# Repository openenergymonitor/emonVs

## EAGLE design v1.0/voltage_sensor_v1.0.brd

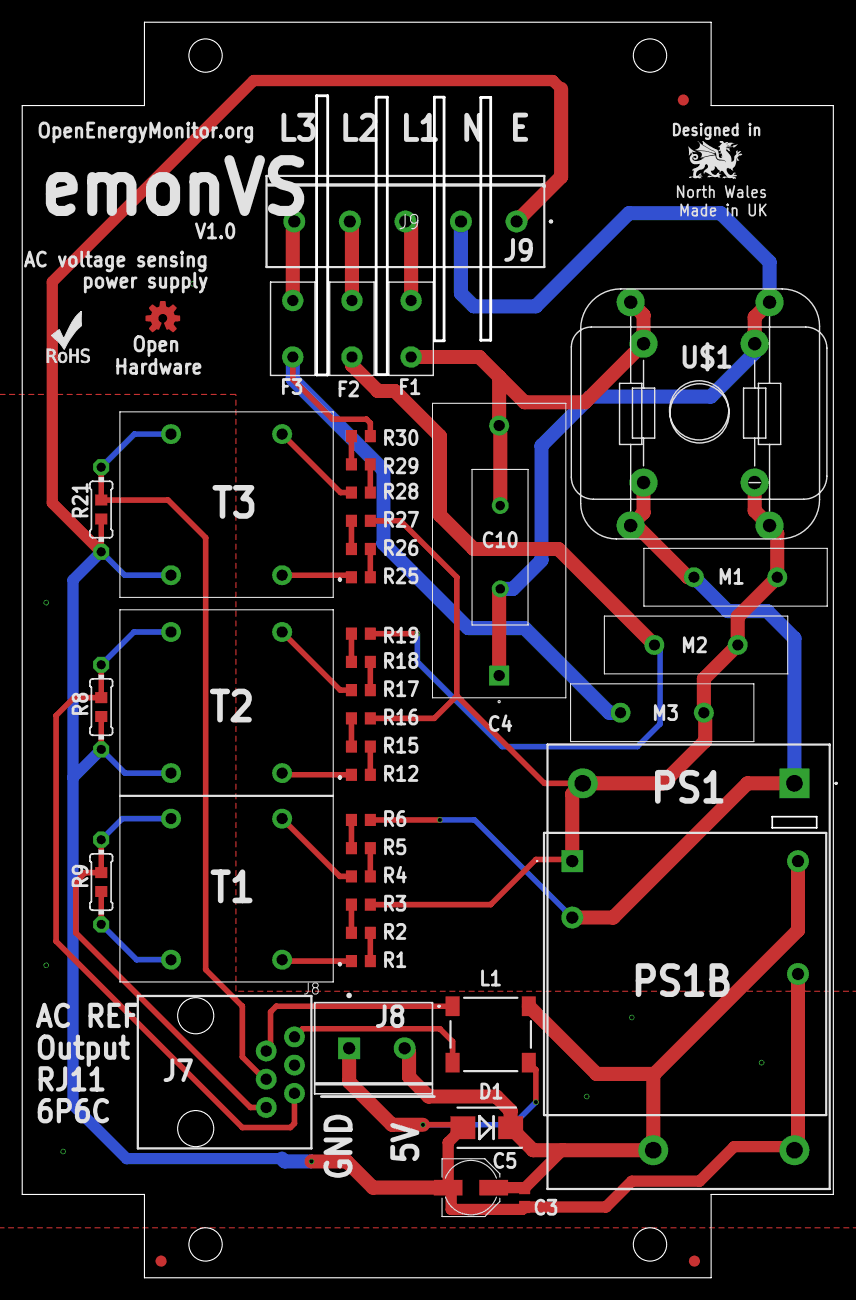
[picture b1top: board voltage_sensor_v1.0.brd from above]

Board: 2 copper layers, 73.0 x 113.0 mm, 51 parts (0 on the bottom side), 34 nets.

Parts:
C3: 1uF; C0603
C4: B32923C3105M000; B32923C_(26.5_X_12)
C5: 180uF; PANASONIC_C
C10: DE2F3KY103MA3BM02F
D1: SMBJ7.0A; DIOM5336X244N
F1, F2, F3: 2A/250V; BELFUSE1A
FD1, FD2, FD3: FIDUCIAL1X2; FIDUCIAL-1X2
J7: RJ11-6
J8: TE_CONNECTIVITY_282836-2TE_CONNECTIVITY_282836-2_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; TE_CONNECTIVITY_282836-2_0
J9: 282836-5; 2828365
L1: 744252101
LOGO1: ROHS_LOGO; ROHS_LOGO_0.18_IN
LOGO2: OSHW-LOGOS-COPPER; OSHW-LOGO-S_COPPER
M1, M2, M3: MOV-14D431KTR; MOV14D431KTR
PS1: MP-LD10-23B05R2; MPLD1023B12R2
PS1B: MP-LD05-23B05R2; MPLD0523B03R2
R1, R2, R3, R4, R5, R6, R12, R15, R16, R17, R18, R19, R25, R26, R27, R28, R29, R30: 10k; R0603
R8, R9, R21: 75R; R0603
R8B, R9B, R21B: 0204/7
T1, T2, T3: ZMPT101B
U$1: 47mH; RN114-0.3-02-47M
U$1B: RN214-0.3-02-47M

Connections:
5V: C3.1, C5.+, D1.1, J8.2, L1.6, PS1.4, PS1B.5
GND: C3.2, C5.-, D1.2, J8.1, J9.1, L1.4, PS1.6, PS1B.4, R8.2, R8B.2, R9.2, R9B.2, R21.2, R21B.2, T1.4, T2.4, T3.4
L1: M1.1, PS1.1, PS1B.2, R6.2, U$1.P$1, U$1B.P$1
L2: F2.OUT, M2.1, R19.2
L3: F3.OUT, M3.1, R30.2
unnamed: R1.1, T1.1
unnamed: R4.1, T1.2
unnamed: R1.2, R2.1
unnamed: R4.2, R5.1
unnamed: R5.2, R6.1
unnamed: R2.2, R3.1
unnamed: F1.IN, J9.3
unnamed: F2.IN, J9.4
unnamed: R12.1, T2.1
unnamed: R17.1, T2.2
unnamed: R12.2, R15.1
unnamed: R17.2, R18.1
unnamed: R18.2, R19.1
unnamed: R15.2, R16.1
unnamed: F3.IN, J9.5
unnamed: J7.2, L1.1
unnamed: R25.1, T3.1
unnamed: R28.1, T3.2
unnamed: R25.2, R26.1
unnamed: R28.2, R29.1
unnamed: R29.2, R30.1
unnamed: R26.2, R27.1
unnamed: J7.1, L1.3
unnamed: C4.1, C10.1, J9.2, U$1.P$4, U$1B.P$4
unnamed: C4.2, C10.2, F1.OUT, U$1.P$2, U$1B.P$2
NEUTRAL: M1.2, M2.2, M3.2, PS1.2, PS1B.1, R3.2, R16.2, R27.2, U$1.P$3, U$1B.P$3
VS1: J7.6, R9.1, R9B.1, T1.3
VS2: J7.5, R8.1, R8B.1, T2.3
VS3: J7.4, R21.1, R21B.1, T3.3

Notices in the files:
parts and their libraries:
SparkFun-Connectors: Licensing: CC v3.0 Share-Alike You are welcome to use this library for commercial purposes.
SparkFun-Aesthetics: Licensing: Creative Commons ShareAlike 4.0 International - https://creativecommons.org/licenses/by-sa/4.0
